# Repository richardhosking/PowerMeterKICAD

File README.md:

# PowerMeterKICAD
KICAD files for power/SWR meter

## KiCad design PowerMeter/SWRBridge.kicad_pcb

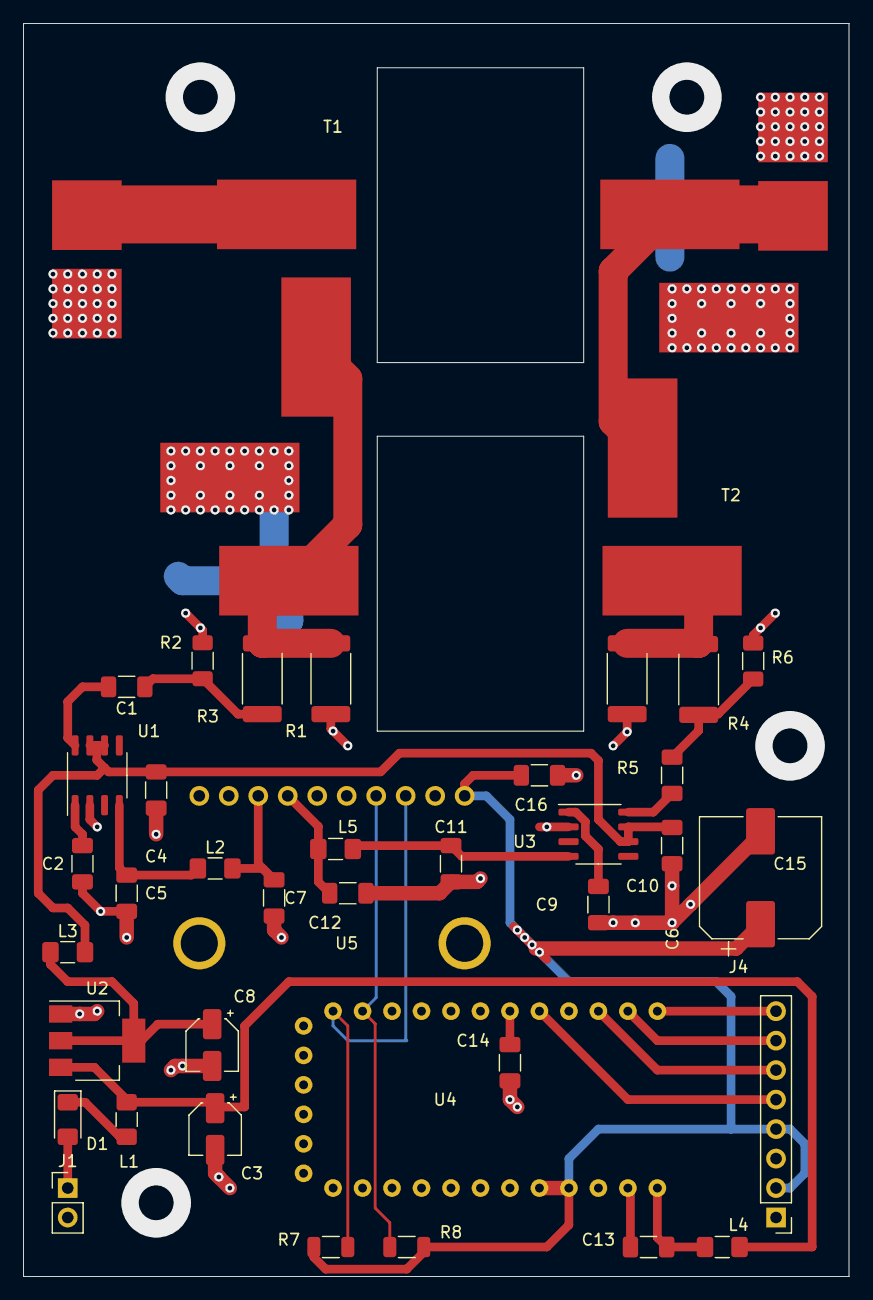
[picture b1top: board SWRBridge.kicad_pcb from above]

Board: 2 copper layers, 71.1 x 108.0 mm, 41 parts (0 on the bottom side), 29 nets.

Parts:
C1, C2, C4, C6, C9, C10, C13, C14, C16: 100n; C_1206_3216Metric_Pad1.33x1.80mm_HandSolder
C3, C8: 10u; CP_Elec_4x5.4
C5, C7, C11, C12: 1n; C_1206_3216Metric_Pad1.33x1.80mm_HandSolder
C15: 220u; CP_Elec_10x10
D1: 1N4001; D_1206_3216Metric_Pad1.42x1.75mm_HandSolder
J1: Power; PinHeader_1x02_P2.54mm_Vertical
J2: Input; Pad
J3: Antenna; Pad
J4: Display; PinHeader_1x08_P2.54mm_Vertical
L1, L2, L3, L4, L5: 100uH; L_1206_3216Metric_Pad1.42x1.75mm_HandSolder
R1, R5: 56R 1W; R_2512_6332Metric_Pad1.40x3.35mm_HandSolder
R2, R6: 56R; R_1206_3216Metric_Pad1.30x1.75mm_HandSolder
R3, R4: 510R 1W; R_2512_6332Metric_Pad1.40x3.35mm_HandSolder
R7, R8: 4K7; R_1206_3216Metric
T1, T2: 1:24T; SWRVoltageTransformer
U1, U3: AD8307; SO-8_3.9x4.9mm_P1.27mm
U2: AP1117-50; SOT-223-3_TabPin2
U4: AdafruitProTrinket3V3; AdafruitTrinketPro3V3
U5: ADS1115Module

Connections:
+5V: C4.1, C10.1, L3.2, U1.6 (ENB), U1.7 (VPS), U3.6 (ENB), U3.7 (VPS)
/3V3: C15.1, C16.1, J4.2, J4.4, R7.1, R8.1, U4.8 (PB0), U4.27 (3V3), U5.8 (VDD)
/Data: J4.6, U4.11 (PB3MOSI)
/DisplayReset: J4.8, U4.9 (PB1)
/DisplaySelect: J4.7, U4.10 (PB2SS)
/Forward: C7.1, L2.2, U5.5 (AIN1)
/Reverse: C12.1, L5.2, U5.4 (AIN0)
/SCLK: J4.5, U4.13 (PB5SCK)
GND: C2.2, C3.2, C4.2, C5.2, C7.2, C8.2, C9.2, C10.2, C11.2, C12.2, C13.2, C14.2, C15.2, C16.2, J1.2, J2.2 (Ext), J3.2 (Ext), J4.1, R1.2, R2.2, R5.1, R6.1, T1.2, T1.5, T2.2, T2.5, U1.2 (COM), U2.1 (GND), U3.2 (COM), U4.20 (GND), U4.21 (GND), U4.29 (GND), U5.1 (ADDR), U5.3 (GND)
unnamed: C1.1, R2.1, R3.2
unnamed: C1.2, U1.8 (INP)
unnamed: C2.1, U1.1 (INM)
unnamed: C3.1, L1.2, L4.1, U2.3 (VI)
unnamed: C5.1, L2.1, U1.4 (OUT)
unnamed: C6.1, R4.2, R6.2
unnamed: C6.2, U3.8 (INP)
unnamed: C8.1, L3.1, U2.2 (VO)
unnamed: C9.1, U3.1 (INM)
unnamed: C11.1, L5.1, U3.4 (OUT)
unnamed: C13.1, L4.2, U4.30 (VBAT)
unnamed: C14.1, U4.31 (AREF)
unnamed: D1.1 (K), L1.1
unnamed: D1.2 (A), J1.1
unnamed: J2.1 (In), T1.3
unnamed: J3.1 (In), T1.4, T2.1
unnamed: R1.1, R3.1, T1.1, T2.4
unnamed: R4.1, R5.2, T2.3
unnamed: R7.2, U4.19 (PC5A5SCL), U5.10 (SCL)
unnamed: R8.2, U4.18 (PC4A4SDA), U5.9 (SDA)

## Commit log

2024-07-09 New version of Power Meter
2024-07-15 Version 2 Add ADS1115 ADC
